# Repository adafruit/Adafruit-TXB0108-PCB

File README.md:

# PCB for the Adafruit TXB0108 breakout board

<a href="http://www.adafruit.com/products/395"><br/>Click here to purchase one from the Adafruit shop</a>

__Format is EagleCAD schematic and board layout__

Because the Arduino (and Basic Stamp) are 5V devices, and most modern sensors, displays, flash cards and modes are 3.3V-only, many makers find that they need to perform level shifting/conversion to protect the 3.3V device from 5V.

Although one can use resistors to make a divider, for high speed transfers, the resistors can add a lot of slew and cause havoc that is tough to debug. For that reason, we like using 4050/74LVX245 series and similar logic to perform proper level shifting. Only problem is that they are only good in one direction which can be a problem for some specialty bi-diectional interfaces and also makes wiring a little hairy.

That's where this lovely chip, the TXB0108 bi-directional level converter comes in! This chip perform bidirectional level shifting from pretty much any voltage to any voltage and will __auto-detect the direction__. Only thing that doesn't work well with this chip is i2c (because it uses strong pullups which confuse auto-direction sensor). If you need to use pullups, you can but they should be at least 50K ohm - the ones internal to AVRs/Arduino are about 100K ohm so those are OK! Its a little more luxurious than a 74LVX245 but if you just don't want to worry about directional pins this is a life saver!

__Since this chip is a special bi-directional level shifter it does not have strong output pins that can drive LEDs or long cables, it's meant to sit on a breadboard between two logic chips!__ If you do not need instant bi-directional support, we suggest the 74LVX245 as below which has strong output drive.

This breakout saves you from having to solder the very fine pitch packages that this chip comes with. We also add 0.1uF caps onto both sides and a 10K pull-up resistor on the output enable pin so you can use it right out of the box!

## License
Adafruit invests time and resources providing this open source design,
please support Adafruit and open-source hardware by purchasing
products from Adafruit!

Designed by Adafruit Industries.
Creative Commons Attribution, Share-Alike license, check license.txt for more information
All text above must be included in any redistribution

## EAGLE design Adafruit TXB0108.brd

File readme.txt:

This is the PCB for the Adafruit TXB0108 breakout board
Format is EagleCAD schematic and board layout

For more details, check out the product page at

-----> http://www.adafruit.com/products/395

Adafruit invests time and resources providing this open source design, 
please support Adafruit and open-source hardware by purchasing 
products from Adafruit!

Designed by Adafruit Industries.  
Creative Commons Attribution, Share-Alike license, check license.txt for more information
All text above must be included in any redistribution

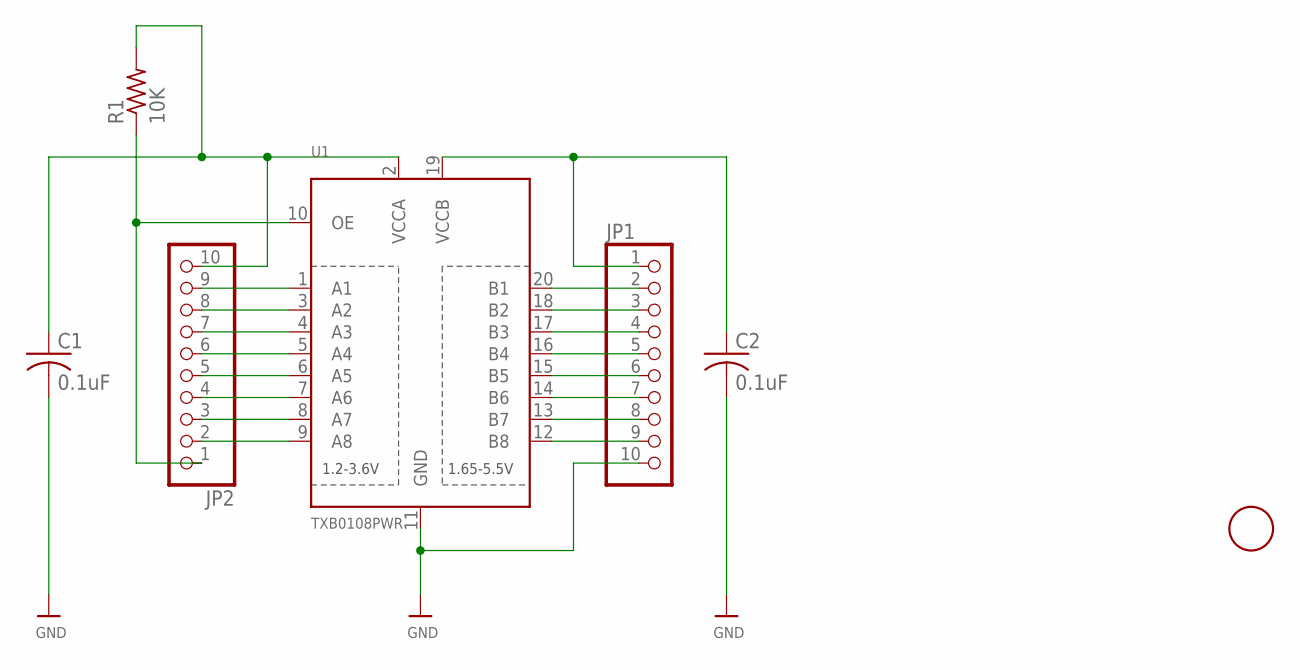
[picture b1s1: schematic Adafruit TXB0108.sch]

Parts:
C1, C2: 0.1uF; C0805
JP1, JP2: HEADER-1X10THICKER; 1X10_ROUND_76
R1: 10K; R0805
U1: TXB0108PWR; TSSOP20
U$6: FIDUCIAL; FIDUCIAL_1MM

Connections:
GND: C1.2, C2.2, JP1.10, U1.11 (GND)
unnamed: JP1.9, U1.12 (B8)
unnamed: JP1.8, U1.13 (B7)
unnamed: JP1.7, U1.14 (B6)
unnamed: JP1.6, U1.15 (B5)
unnamed: JP1.5, U1.16 (B4)
unnamed: JP1.4, U1.17 (B3)
unnamed: JP1.3, U1.18 (B2)
unnamed: JP1.2, U1.20 (B1)
unnamed: C2.1, JP1.1, U1.19 (VCCB)
unnamed: C1.1, JP2.10, R1.2, U1.2 (VCCA)
unnamed: JP2.9, U1.1 (A1)
unnamed: JP2.8, U1.3 (A2)
unnamed: JP2.7, U1.4 (A3)
unnamed: JP2.6, U1.5 (A4)
unnamed: JP2.5, U1.6 (A5)
unnamed: JP2.4, U1.7 (A6)
unnamed: JP2.3, U1.8 (A7)
unnamed: JP2.2, U1.9 (A8)
unnamed: JP2.1, R1.1, U1.10 (OE)

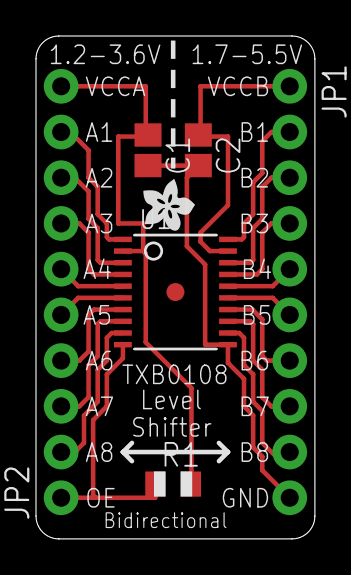
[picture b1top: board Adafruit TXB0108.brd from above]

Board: 2 copper layers, 15.5 x 27.9 mm, 8 parts (0 on the bottom side), 20 nets.

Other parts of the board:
U$4: ADAFRUIT200MIL

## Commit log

2012-08-06 init
2012-08-06 read
2014-12-21 added pdf / png files for fast viewing
2019-04-17 readme + image
2026-06-03 update file format to XML
